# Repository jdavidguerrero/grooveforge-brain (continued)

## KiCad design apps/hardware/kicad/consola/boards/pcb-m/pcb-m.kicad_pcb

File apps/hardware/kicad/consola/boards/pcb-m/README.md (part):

# PCB-M — Placa Principal GrooveForge Consola

> Esquemático jerárquico KiCad 10, decisiones **D8–D43 aprobadas por Juan (2026-11-12; D40 actualizado 2026-11-13)**
> (`apps/docs/consola/24-placa-principal.md` §8). Sin layout PCB; no es aprobación de fabricación.
> Descripción eléctrica: `tools/schgen/pcb_m.py`. Firmware: `apps/consola/surface/include/consola_s/ConsolaMap.h`
> y `apps/docs/consola/17-mapa-pines-teensy.md`. Conector fabricado: `../CONNECTORS.md`.

No habrá PCB-N: jog, pots IN/CUE/MASTER, selector y audífonos son componentes de panel por cable.
PCB-M no lleva MCP23017: **0x20 está en PCB-A; 0x21/0x22/0x23 en la PCB-K única**, que reemplaza
K1/K2. JOG_A/B van a Teensy 37/40; JOG_CLICK y PEDAL_BTN viajan por J_PCB_K al MCP 0x23.

## Bloques (10 subhojas)

| # | Hoja | Contenido |
|---|---|---|
| 01 | `01-teensy` | Sockets Teensy 4.1 y Audio Shield Rev D (módulos); I2S interno |
| 02 | `02-analog-front` | Frente Studio: pad 33k/12k/5.1k, polos A/B del selector por cable, acople 1µF, 1k, BAT54S, bias 100k a VREF; MCP6004 seguidores L/R/VREF; LINE OUT 10µF + 47k sin buffer; divisor PAD_SEL 10k/10k |
| 03 | `03-adc` | ADS1115 0x48 faders AIN0–3; 0x49 expresión/Sharp |
| 04 | `04-mcp-io` | **Vacía**, reservada; MCP 0x23 vive en PCB-K |
| 05 | `05-cv-dac` | MCP4725 0x60/0x61, MCP6004 ganancia 1,5; 1k serie + BAT54S por CV |
| 06 | `06-surface` | JST-PH para jog, pots, selector, HP y FSR; RC 1k/100nF por pot |
| 07 | `07-midi` | **Todo DNP**, reserva sin agujeros/mazos: opto 6N138 y polarización; JST-PH para MIDI TRS **tipo A**, OUT 33Ω/10Ω |
| 08 | `08-connectors-panel` | IDC PCB-A, Qwiic, Serial7 M4, PCB-K, Sharp/expresión |
| 09 | `09-connectors-rear` | JST-PH hacia LINE IN/OUT, CV, pedal; E-drum DNP |
| 11 | `11-diagnostics` | TP, puentes de servicio, indicadores y selección de pull-ups locales |
| 12 | `12-i2c-branches` | PCA9517A ×2, EN_K pin0 / EN_A pin1, pull-ups B, 47 Ω y USBLC6-2SC6 |
| 10 | `10-power` | J_5V_LED_IN → F1; LDO +3.3VA; NT1 AGND/GND; buffer LED y pull-ups I2C |

## Cross-reference: Teensy ↔ señales de PCB-A y panel (D8)

**Manda el pinout de PCB-A ya fabricada**, no la antigua columna Teensy de CONNECTORS.md.
Cinta IDC **1:1**. PCB-M distribuye cada señal al pin que usa el firmware actual:

| Teensy | Función | Net PCB-M | Ruta |
|---|---|---|---|
| T0 / T1 | EN_K / EN_A | `EN_K_GPIO` / `EN_A_GPIO` | Cada rama por su SJ_EN_K_GPIO / SJ_EN_A_GPIO y pull-up 10k (D30); MIDI DNP |
| T2 / T3 | ENC1 A/B | `ENC1_A` / `ENC1_B` | J1_PCBA **5 / 7** |
| T4 / T5 | ENC2 A/B | `ENC2_A` / `ENC2_B` | J1_PCBA **9 / 10** |
| T6 / T9 | ENC3 A/B | `ENC3_A` / `ENC3_B` | J1_PCBA **13 / 15** |
| T10 / T11 | ENC4 A/B | `ENC4_A` / `ENC4_B` | J1_PCBA **17 / 19** |
| T12 / T30 | ENC5 A/B | `ENC5_A` / `ENC5_B` | J1_PCBA **8 / 21** |
| T31 / T32 | ENC6 A/B | `ENC6_A` / `ENC6_B` | J1_PCBA **23 / 25** |
| T33 / T34 | ENC7 A/B | `ENC7_A` / `ENC7_B` | J1_PCBA **28 / 29** |
| T35 / T36 | ENC8 A/B | `ENC8_A` / `ENC8_B` | J1_PCBA **27 / 24** |
| T13 | LEDs teclas | `LED_DATA` | 74AHCT1G125 → `LED_DIN_5V` → **J_PCB_K.6**; J1.26 NC |
| T14–T17 | FSR velocity 1–4 | `FSR1_ADC`–`FSR4_ADC` | J_FSR1–4, divisor 10k a GND |
| T18 / T19 | I2C SDA/SCL | `I2C_SDA` / `I2C_SCL` | lado A de PCA9517A y convertidores; B_A → J2_I2C.3/.4; B_K → J_PCB_K.2/.4 |
| T22 | MASTER | `POT_MASTER` | J_POT_MASTER.2 → **1k → ADC; 100nF a GND** |
| T24 | CUE | `POT_CUE` | J_POT_CUE.2 → **1k → ADC; 100nF a GND** |
| T26 | IN | `POT_IN` | J_POT_IN.2 → **1k → ADC; 100nF a GND** |
| T28 / T29 | M4 RX/TX Serial7 | `M4_RX7` / `M4_TX7` | J3_M4.3 / .4 ↔ pads SDA/TX M4 / SCL/RX M4, vía 1 kΩ cada línea |
| T37 / T40 | Jog A/B | `JOG_A` / `JOG_B` | J_JOG.2/.3; clic por .4 hacia PCB-K |
| T41 | Selector pad | `PAD_SEL_ADC` | J_PAD_SEL.2 y divisor permanente 10k/10k |
| T7 / T8 / T20 / T21 / T23 | I2S TX/RX/LRCLK/BCLK/MCLK | `I2S_*` | Internos al módulo Audio Shield; sin ruta al panel |
| T25 / T27 / T38 / T39 | E-drum reservado | NC | No se asigna función nueva; J_EDRUM DNP |

| Señal de PCB-A | J1_PCBA | Destino PCB-M |
|---|---|---|
| FADER1 / FADER2 / FADER3 / FADER4 | **16 / 14 / 12 / 11** | U_ADS1 **AIN0 / AIN1 / AIN2 / AIN3** (pines 4/5/6/7), dirección **0x48** |
| +5V | 1 / 2 | +5V_LED después de F1 |
| GND | 3 / 4 / 6 | GND |
| +3V3 | 30 | +3.3V digital |
| Spare | **18** | **NC**, sin uso |
| INT_K / INT_A | **20 / 22** | **NC**, MCP por sondeo I2C |
| LED_DIN | **26** | **NC**, LED solo por J_PCB_K |

**I2C no va por el IDC J1:** llega a PCB-A por J2. La PCB-A fabricada no se modifica salvo
**desoldar R1/R2** al instalar PCB-M (D14). No conectar además la antigua cadena PCB-A J4 → K1/K2
al usar la nueva PCB-K por J_PCB_K.

## Conectores hacia panel y otras placas

PH = JST-PH 2,0 mm; normalmente BnB-PH-K vertical. J_5V_LED_IN usa S2B-PH-K horizontal de la BOM.

| Ref | Tipo | Pines en orden 1→n |
|---|---|---|
| J1_PCBA | IDC 2×15 | Pinout fabricado de CONNECTORS.md; destinos en tablas anteriores |
| J2_I2C | JST-SH 4 Qwiic | GND / +3.3V / SDA / SCL |
| J3_M4 | PH 4 | GND / **NC** / M4_RX7_CABLE / M4_TX7_CABLE; pads M4 por rótulo (D40), vía 1 kΩ por señal; M4 por USB propio |
| J_PCB_K | PH 10 C158038 | +3.3V / SDA_B_K / GND / SCL_B_K / GND / LED_DIN_5V / GND / +5V_LED_K / JOG_CLICK / PEDAL_BTN |
| J5_SHARP1, J6_SHARP2 | PH 3 cada uno | +5V_LED / SHARPx_RAW / GND; 10k serie hacia ADS |
| J7_EXP1, J8_EXP2 | PH 2 cada uno | +3.3V / EXPx_ADC, pulldown 10k |
| J_JOG | PH 4 | GND / JOG_A / JOG_B / JOG_CLICK |
| J_POT_MASTER/CUE/IN | PH 3 cada uno | +3.3V / POT_x_WIPER / GND; cursor **antes** del RC |
| J_PAD_SEL | PH 3 | +3.3V / PAD_SEL_ADC / GND |
| J_FSR1–4 | PH 2 cada uno | +3.3V / FSRx_ADC; pulldown 10k |
| J_5V_LED_IN | PH 2 S2B-PH-K | **+5V_LED_RAW / GND** desde cable USB-A del Pi |
| J_5V_BKUP | PH 2, **DNP** | +5V_LED_RAW / GND; solo alternativa, no conectar ambas entradas |
| J_EDRUM | PH 5, **DNP** | Todos NC |

### Cableado jack ↔ JST-PH (D15)

Los jacks se compran en **Bogotá**, se fijan **con tuerca a la pared trasera del cuerpo** y van
por cable a los JST-PH del borde trasero de PCB-M. No hay jacks montados en esta PCB. Las hojas
06/07/09 son agrupaciones eléctricas: colocar J_HP en el borde trasero; JST MIDI DNP, sin mazos ni agujeros
cuando se haga layout. Confirmar por continuidad los terminales del jack comprado antes de soldar;
la tabla usa **T = tip/punta, R = ring/anillo, S = sleeve/manguito**, no la numeración de sus patillas.

| Jack externo | Ref en PCB-M | JST-PH | Cableado hacia contactos del jack |
|---|---|---|---|
| LINE IN L 6,35 mm TRS | J_LINE_IN_L | B3B-PH-K, 3 vías | **1→T** LINE_IN_L_T, **2→R** LINE_IN_L_R, **3→S** AGND |
| LINE IN R 6,35 mm TRS | J_LINE_IN_R | B3B-PH-K, 3 vías | **1→T** LINE_IN_R_T, **2→R** LINE_IN_R_R, **3→S** AGND |
| LINE OUT L 6,35 mm TS/TRS | J_LINE_OUT_L | B3B-PH-K, 3 vías | **1→T** LINE_OUT_L_T después de 10µF, **2 NC**, **3→S** AGND; ring sin cable si es TRS |
| LINE OUT R 6,35 mm TS/TRS | J_LINE_OUT_R | B3B-PH-K, 3 vías | **1→T** LINE_OUT_R_T después de 10µF, **2 NC**, **3→S** AGND; ring sin cable si es TRS |
| PEDAL 6,35 mm TRS | J_PEDAL | B3B-PH-K, 3 vías | **1→T** PEDAL_RAW (1k → PEDAL_BTN protegido), **2 NC** (R sin cable), **3→S** GND |
| CV1 3,5 mm TS | J_CV1 | B2B-PH-K, 2 vías | **1→T** CV1_PROTECTED, **2→S** AGND |
| CV2 3,5 mm TS | J_CV2 | B2B-PH-K, 2 vías | **1→T** CV2_PROTECTED, **2→S** AGND |
| MIDI IN 3,5 mm TRS **tipo A** | J_MIDI_IN | B3B-PH-K, 3 vías | **1→T** MIDI_IN_TIP (DIN5), **2→R** MIDI_IN_RING (DIN4), **3 NC** (sleeve/DIN2 sin cable) |
| MIDI OUT 3,5 mm TRS **tipo A** | J_MIDI_OUT | B3B-PH-K, 3 vías | **1→T** MIDI_OUT_TIP (DIN5), **2→R** MIDI_OUT_RING (DIN4), **3→S** GND (DIN2) |
| Audífonos cue 6,35 mm TRS | **J_HP** (06) | B3B-PH-K, 3 vías | **1→T** HP_L, **2→R** HP_R, **3→S** HP_VGND |

**HP_VGND es una salida activa del SGTL5000, nunca GND/AGND.** Se elimina el duplicado J_HP_CUE:
J_HP es el único conector hacia el jack de audífonos que ya iba por cable.
**Detección de inserción:** los símbolos anteriores eran AudioJack2/3 sin switches; ninguno tenía
pin ni red de detección. Por tanto se conservan todos sus contactos actuales y no se inventa un
pin de detección. Si el jack adquirido trae contactos conmutados, dejarlos sin cable y verificar
que T/R/S se identificaron correctamente. **LINE IN ring sigue sin terminación balanceada definida**;
se conserva la red por cable, pendiente de decisión eléctrica antes de fabricar.

### Selector en panel (D13)

R_SEL_T/R_SEL_B de 10k quedan en PCB-M: +3.3V → 10k → **PAD_SEL_ADC** → 10k → GND.
Se elimina **SW_PAD_SEL**. Cablear el **común del polo C** a J_PAD_SEL.2, sus contactos extremos
a .3 (GND) y .1 (+3,3 V), y **dejar el contacto central sin cable**. Lectura 0 / 1,65 / 3,3 V;
no se necesita un cuarto hilo ni una escalera en el panel. La correspondencia con 0/−10/−20 dB
se verifica con los polos A/B y el firmware en banco.
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
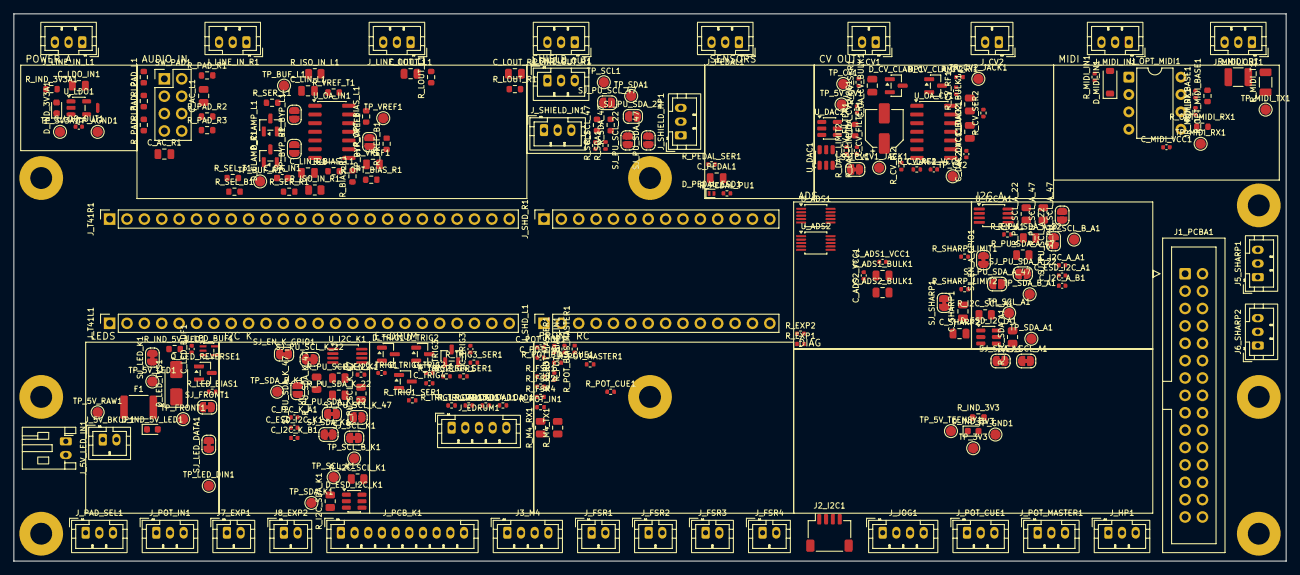
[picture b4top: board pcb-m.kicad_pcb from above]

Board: 2 copper layers, 186.0 x 80.0 mm, 254 parts (0 on the bottom side), 156 nets, no tracks yet.

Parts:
C_AC_L1: 1uF; C_0805_2012Metric
C_AC_R1: 1uF; C_0805_2012Metric
C_ADS1_BULK1, C_ADS2_BULK1: 10uF; C_0805_2012Metric
C_ADS1_VCC1, C_ADS2_VCC1: 100nF; C_0402_1005Metric
C_CV_FILTER1: 47uF 16V; CP_Elec_5x5.4
C_DAC1_BULK1, C_DAC2_BULK1: 10uF; C_0805_2012Metric
C_DAC1_VCC1, C_DAC2_VCC1: 100nF; C_0402_1005Metric
C_ESD_I2C_A1, C_ESD_I2C_K1: 100nF; C_0402_1005Metric
C_I2C_A_A1, C_I2C_A_B1, C_I2C_K_A1, C_I2C_K_B1: 100nF; C_0402_1005Metric
C_LDO_IN1: 10uF; C_0805_2012Metric
C_LDO_OUT1: 1uF; C_0402_1005Metric
C_LED_BUF1: 100nF; C_0402_1005Metric
C_LIN_L1: 4.7uF; C_0805_2012Metric
C_LIN_R1: 4.7uF; C_0805_2012Metric
C_LOUT_L1: 10uF; C_0805_2012Metric
C_LOUT_R1: 10uF; C_0805_2012Metric
C_MIDI_VCC1: 100nF; C_0402_1005Metric
C_OA_CV_BULK1: 10uF; C_0805_2012Metric
C_OA_CV_VCC1: 100nF; C_0402_1005Metric
C_OA_IN1: 100nF; C_0603_1608Metric
C_PEDAL1: 10nF; C_0805_2012Metric
C_POT_CUE1: 100nF; C_0402_1005Metric
C_POT_IN1: 100nF; C_0402_1005Metric
C_POT_MASTER1: 100nF; C_0402_1005Metric
C_SHARP1, C_SHARP2: 10uF; C_0805_2012Metric
C_TRIG1, C_TRIG2, C_TRIG3, C_TRIG4: DNP; C_0402_1005Metric
C_VREF1: 10uF; C_0805_2012Metric
D_CLAMP_L1: BAT54S; SOT-23
D_CLAMP_R1: BAT54S; SOT-23
D_CV_CLAMP1, D_CV_CLAMP2: BAT54S; SOT-23
D_ESD_I2C_A1, D_ESD_I2C_K1: USBLC6-2SC6; SOT-23-6
D_IND_3V3, D_IND_3V3A1, D_IND_5V_LED1: RED ~1mA; LED_0603_1608Metric
D_LED_TVS1: SMAJ5.0A; D_SMA_K1
D_MIDI_IN1: 1N4148W; D_SOD-123
D_PEDAL_ESD1: PESD3V3U1UL,315; D_SOD-882_K1
D_TRIG1, D_TRIG2, D_TRIG3, D_TRIG4: BAT54S; SOT-23
F1: 0.75A MF-MSMF075/24-2; Fuse_1812_4532Metric
H1, H2, H3, H4, H5, H6, H7, H8: M3 to floor tower; MountingHole_3.2mm_M3_Pad
J1_PCBA1: IDC_2x15_PCB-A; IDC-Header_2x15_P2.54mm_Vertical
J2_I2C1: JST-SH_4pin_I2C; JST_SH_SM04B-SRSS-TB_1x04-1MP_P1.00mm_Horizontal
J3_M4: JST-PH_4pin_M4; JST_PH_B4B-PH-K_1x04_P2.00mm_Vertical
J5_SHARP1: JST-PH_3pin_Sharp1; JST_PH_B3B-PH-K_1x03_P2.00mm_Vertical
J6_SHARP2: JST-PH_3pin_Sharp2; JST_PH_B3B-PH-K_1x03_P2.00mm_Vertical
J7_EXP1: JST-PH_2pin_EXP1; JST_PH_B2B-PH-K_1x02_P2.00mm_Vertical
J8_EXP2: JST-PH_2pin_EXP2; JST_PH_B2B-PH-K_1x02_P2.00mm_Vertical
JP_BYP_L1: BYP L (sin U_OA_IN); SolderJumper-2_P1.3mm_Open_RoundedPad1.0x1.5mm
JP_BYP_R1: BYP R (sin U_OA_IN); SolderJumper-2_P1.3mm_Open_RoundedPad1.0x1.5mm
JP_BYP_VREF1: BYP VREF (sin U_OA_IN); SolderJumper-2_P1.3mm_Open_RoundedPad1.0x1.5mm
J_5V_BKUP1: 5V_BACKUP_DNP; JST_PH_B2B-PH-K_1x02_P2.00mm_Vertical
J_5V_LED_IN1: USB-A_PI_5V_LED_IN; JST_PH_S2B-PH-K_1x02_P2.00mm_Horizontal
J_CV1: CV1_PANEL_CABLE; JST_PH_B2B-PH-K_1x02_P2.00mm_Vertical
J_CV2: CV2_PANEL_CABLE; JST_PH_B2B-PH-K_1x02_P2.00mm_Vertical
J_EDRUM1: EDRUM_RESERVED_DNP; JST_PH_B5B-PH-K_1x05_P2.00mm_Vertical
J_FSR1: JST-PH_2pin_FSR1; JST_PH_B2B-PH-K_1x02_P2.00mm_Vertical
J_FSR2: JST-PH_2pin_FSR2; JST_PH_B2B-PH-K_1x02_P2.00mm_Vertical
J_FSR3: JST-PH_2pin_FSR3; JST_PH_B2B-PH-K_1x02_P2.00mm_Vertical
J_FSR4: JST-PH_2pin_FSR4; JST_PH_B2B-PH-K_1x02_P2.00mm_Vertical
J_HP1: HP_CABLE; JST_PH_B3B-PH-K_1x03_P2.00mm_Vertical
J_JOG1: JOG_CABLE; JST_PH_B4B-PH-K_1x04_P2.00mm_Vertical
J_LINE_IN_L1: LINE_IN_L_PANEL_CABLE; JST_PH_B3B-PH-K_1x03_P2.00mm_Vertical
J_LINE_IN_R1: LINE_IN_R_PANEL_CABLE; JST_PH_B3B-PH-K_1x03_P2.00mm_Vertical
J_LINE_OUT_L1: LINE_OUT_L_PANEL_CABLE; JST_PH_B3B-PH-K_1x03_P2.00mm_Vertical
J_LINE_OUT_R1: LINE_OUT_R_PANEL_CABLE; JST_PH_B3B-PH-K_1x03_P2.00mm_Vertical
J_MIDI_IN1: MIDI_IN_PANEL_CABLE; JST_PH_B3B-PH-K_1x03_P2.00mm_Vertical
J_MIDI_OUT1: MIDI_OUT_PANEL_CABLE; JST_PH_B3B-PH-K_1x03_P2.00mm_Vertical
J_PAD_SEL1: PAD_SEL_CABLE; JST_PH_B3B-PH-K_1x03_P2.00mm_Vertical
J_PCB_K1: PCB_K_KEY_CABLE; JST_PH_B10B-PH-K_1x10_P2.00mm_Vertical
J_PEDAL1: PEDAL_PANEL_CABLE; JST_PH_B3B-PH-K_1x03_P2.00mm_Vertical
J_POT_CUE1: POT_CUE_CABLE; JST_PH_B3B-PH-K_1x03_P2.00mm_Vertical
J_POT_IN1: POT_IN_CABLE; JST_PH_B3B-PH-K_1x03_P2.00mm_Vertical
J_POT_MASTER1: POT_MASTER_CABLE; JST_PH_B3B-PH-K_1x03_P2.00mm_Vertical
J_SHD_L1: AudioShieldRevD-L; PinSocket_1x14_P2.54mm_Vertical
J_SHD_R1: AudioShieldRevD-R; PinSocket_1x14_P2.54mm_Vertical
J_SHIELD_HP1: HP L/R/VGND - NEVER GND; JST_PH_B3B-PH-K_1x03_P2.00mm_Vertical
J_SHIELD_IN1: SHIELD pads LINE IN L/R/G; JST_PH_B3B-PH-K_1x03_P2.00mm_Vertical
J_SHIELD_OUT1: SHIELD pads LINE OUT L/R/G; JST_PH_B3B-PH-K_1x03_P2.00mm_Vertical
J_T41L1: Teensy41-LeftRow; PinSocket_1x24_P2.54mm_Vertical
J_T41R1: Teensy41-RightRow; PinSocket_1x24_P2.54mm_Vertical
NT1: NetTie_2; NetTie-2_SMD_Pad0.5mm
Q_LED_REVERSE1: AO3401A; SOT-23
R_BIAS_L1: 100k; R_0603_1608Metric
R_BIAS_R1: 100k; R_0603_1608Metric
R_CV_FILTER1: 10; R_0603_1608Metric
R_CV_RF1, R_CV_RF2: 10k; R_0402_1005Metric
R_CV_RI1, R_CV_RI2: 20k; R_0402_1005Metric
R_CV_SER1, R_CV_SER2: 1k; R_0402_1005Metric
R_DAC_LIMIT1, R_DAC_LIMIT2: 2.2k; R_0402_1005Metric
R_EN_A1: 10k; R_0402_1005Metric
R_EN_K1: 10k; R_0402_1005Metric
R_EXP1, R_EXP2: 10k; R_0402_1005Metric
R_FSR1, R_FSR2, R_FSR3, R_FSR4: 10k; R_0402_1005Metric
R_I2C_SCL_A1, R_I2C_SCL_K1, R_I2C_SDA_A1, R_I2C_SDA_K1: 47; R_0805_2012Metric
R_IND_3V3, R_IND_3V3A1: 1.5k; R_0603_1608Metric
R_IND_5V_LED1: 3.3k; R_0603_1608Metric
R_ISO_IN_L1: 0; R_0805_2012Metric
R_ISO_IN_R1: 0; R_0805_2012Metric
R_LED_BIAS1: 100k; R_0402_1005Metric
R_LOUT_L1: 47k; R_0603_1608Metric
R_LOUT_R1: 47k; R_0603_1608Metric
R_M4_RX1, R_M4_TX1: 1k; R_0805_2012Metric
R_MIDI_BASE1: 10k; R_0402_1005Metric
R_MIDI_IN1: 220; R_0402_1005Metric
R_MIDI_R1: 33; R_1210_3225Metric
R_MIDI_RX1: 4.7k; R_0402_1005Metric
R_MIDI_T1: 10; R_1206_3216Metric
R_OPT_BIAS_L1: DNP tune parallel; R_0603_1608Metric
R_OPT_BIAS_R1: DNP tune parallel; R_0603_1608Metric
R_OPT_MIDI_BASE1: DNP tune parallel; R_0603_1608Metric
R_OPT_MIDI_RX1: DNP tune parallel; R_0603_1608Metric
R_PAD_L1: 33k; R_0603_1608Metric
R_PAD_L2: 12k; R_0603_1608Metric
R_PAD_L3: 5.1k; R_0603_1608Metric
R_PAD_R1: 33k; R_0603_1608Metric
R_PAD_R2: 12k; R_0603_1608Metric
R_PAD_R3: 5.1k; R_0603_1608Metric
R_PEDAL_PU1: 10k; R_0402_1005Metric
R_PEDAL_SER1: 1k; R_0402_1005Metric
R_POT_BIAS_CUE1: 100k; R_0402_1005Metric
R_POT_BIAS_IN1: 100k; R_0402_1005Metric
R_POT_BIAS_MASTER1: 100k; R_0402_1005Metric
R_POT_CUE1: 1k; R_0402_1005Metric
R_POT_IN1: 1k; R_0402_1005Metric
R_POT_MASTER1: 1k; R_0402_1005Metric
R_PU_SCL_A_22: 2.2k; R_0805_2012Metric
R_PU_SCL_A_47: 4.7k; R_0805_2012Metric
R_PU_SCL_K_22: 2.2k; R_0805_2012Metric
R_PU_SCL_K_47: 4.7k; R_0805_2012Metric
R_PU_SDA_A_22: 2.2k; R_0805_2012Metric
R_PU_SDA_A_47: 4.7k; R_0805_2012Metric
R_PU_SDA_K_22: 2.2k; R_0805_2012Metric
R_PU_SDA_K_47: 4.7k; R_0805_2012Metric
R_SCL1: 2.2k; R_0402_1005Metric
R_SCL_47: 4.7k; R_0603_1608Metric
R_SDA1: 2.2k; R_0402_1005Metric
R_SDA_47: 4.7k; R_0603_1608Metric
R_SEL_B1: 10k; R_0603_1608Metric
R_SEL_T1: 10k; R_0603_1608Metric
R_SER_L1: 1k; R_0603_1608Metric
R_SER_R1: 1k; R_0603_1608Metric
R_SHARP_LIMIT1, R_SHARP_LIMIT2: 10k; R_0402_1005Metric
R_TRIG1_LOAD1, R_TRIG2_LOAD1, R_TRIG3_LOAD1, R_TRIG4_LOAD1: 1M; R_0402_1005Metric
R_TRIG1_SER1, R_TRIG2_SER1, R_TRIG3_SER1, R_TRIG4_SER1: 1k; R_0402_1005Metric
R_VREF_B1: 10k; R_0603_1608Metric
R_VREF_T1: 10k; R_0603_1608Metric
SJ_CV1: SJ_CV; SolderJumper-2_P1.3mm_Bridged_RoundedPad1.0x1.5mm
SJ_EN_A_GPIO1: SJ_EN_A_GPIO; SolderJumper-2_P1.3mm_Bridged_RoundedPad1.0x1.5mm
SJ_EN_K_GPIO1: SJ_EN_K_GPIO; SolderJumper-2_P1.3mm_Bridged_RoundedPad1.0x1.5mm
SJ_FRONT1: SJ_FRONT; SolderJumper-2_P1.3mm_Bridged_RoundedPad1.0x1.5mm
SJ_LED_DATA1: SJ_LED_DATA; SolderJumper-2_P1.3mm_Bridged_RoundedPad1.0x1.5mm
SJ_LED_K1: SJ_LED_K; SolderJumper-2_P1.3mm_Bridged_RoundedPad1.0x1.5mm
SJ_PU_SCL_22: SJ_PU_SCL_22; SolderJumper-2_P1.3mm_Open_RoundedPad1.0x1.5mm
SJ_PU_SCL_47: SJ_PU_SCL_47; SolderJumper-2_P1.3mm_Open_RoundedPad1.0x1.5mm
SJ_PU_SCL_A_22: SJ_PU_SCL_A_22; SolderJumper-2_P1.3mm_Bridged_RoundedPad1.0x1.5mm
SJ_PU_SCL_A_47: SJ_PU_SCL_A_47; SolderJumper-2_P1.3mm_Open_RoundedPad1.0x1.5mm
SJ_PU_SCL_K_22: SJ_PU_SCL_K_22; SolderJumper-2_P1.3mm_Bridged_RoundedPad1.0x1.5mm
SJ_PU_SCL_K_47: SJ_PU_SCL_K_47; SolderJumper-2_P1.3mm_Open_RoundedPad1.0x1.5mm
SJ_PU_SDA_22: SJ_PU_SDA_22; SolderJumper-2_P1.3mm_Open_RoundedPad1.0x1.5mm
SJ_PU_SDA_47: SJ_PU_SDA_47; SolderJumper-2_P1.3mm_Open_RoundedPad1.0x1.5mm
SJ_PU_SDA_A_22: SJ_PU_SDA_A_22; SolderJumper-2_P1.3mm_Bridged_RoundedPad1.0x1.5mm
SJ_PU_SDA_A_47: SJ_PU_SDA_A_47; SolderJumper-2_P1.3mm_Open_RoundedPad1.0x1.5mm
SJ_PU_SDA_K_22: SJ_PU_SDA_K_22; SolderJumper-2_P1.3mm_Bridged_RoundedPad1.0x1.5mm
SJ_PU_SDA_K_47: SJ_PU_SDA_K_47; SolderJumper-2_P1.3mm_Open_RoundedPad1.0x1.5mm
SJ_SCL_A1: SJ_SCL_A; SolderJumper-2_P1.3mm_Bridged_RoundedPad1.0x1.5mm
SJ_SCL_K1: SJ_SCL_K; SolderJumper-2_P1.3mm_Bridged_RoundedPad1.0x1.5mm
SJ_SDA_A1: SJ_SDA_A; SolderJumper-2_P1.3mm_Bridged_RoundedPad1.0x1.5mm
SJ_SDA_K1: SJ_SDA_K; SolderJumper-2_P1.3mm_Bridged_RoundedPad1.0x1.5mm
SJ_SHARP1: SJ_SHARP; SolderJumper-2_P1.3mm_Bridged_RoundedPad1.0x1.5mm
SW_PAD1: PAD 3P3T A/B; PinHeader_2x04_P2.54mm_Vertical
TP_3V3: +3.3V; TestPoint_Pad_D1.5mm
TP_3V3A1: +3.3VA; TestPoint_Pad_D1.5mm
TP_5V_CV1: +5V_CV; TestPoint_Pad_D1.5mm
TP_5V_LED1: +5V_LED; TestPoint_Pad_D1.5mm
TP_5V_RAW1: +5V_LED_RAW; TestPoint_Pad_D1.5mm
TP_5V_TEENSY1: +5V_TEENSY; TestPoint_Pad_D1.5mm
TP_AGND1: AGND; TestPoint_Pad_D1.5mm
TP_BUF_L1: BUF_L; TestPoint_Pad_D1.5mm
TP_BUF_R1: BUF_R; TestPoint_Pad_D1.5mm
TP_CV1: CV1_OUT; TestPoint_Pad_D1.5mm
TP_CV1_JACK1: CV1_PROTECTED; TestPoint_Pad_D1.5mm
TP_CV2: CV2_OUT; TestPoint_Pad_D1.5mm
TP_CV2_JACK1: CV2_PROTECTED; TestPoint_Pad_D1.5mm
TP_FRONT1: +3.3VA_FRONT; TestPoint_Pad_D1.5mm
TP_GND1: GND; TestPoint_Pad_D1.5mm
TP_LED_DIN1: LED_DIN_5V; TestPoint_Pad_D1.5mm
TP_MIDI_RX1: MIDI_RX; TestPoint_Pad_D1.5mm
TP_MIDI_TX1: MIDI_TX; TestPoint_Pad_D1.5mm
TP_SCL1: I2C_SCL; TestPoint_Pad_D1.5mm
TP_SCL_A1: I2C_SCL_A; TestPoint_Pad_D1.5mm
TP_SCL_B_A1: I2C_SCL_B_A; TestPoint_Pad_D1.5mm
TP_SCL_B_K1: I2C_SCL_B_K; TestPoint_Pad_D1.5mm
TP_SCL_K1: I2C_SCL_K; TestPoint_Pad_D1.5mm
TP_SDA1: I2C_SDA; TestPoint_Pad_D1.5mm
TP_SDA_A1: I2C_SDA_A; TestPoint_Pad_D1.5mm
TP_SDA_B_A1: I2C_SDA_B_A; TestPoint_Pad_D1.5mm
TP_SDA_B_K1: I2C_SDA_B_K; TestPoint_Pad_D1.5mm
TP_SDA_K1: I2C_SDA_K; TestPoint_Pad_D1.5mm
TP_VREF1: VREF; TestPoint_Pad_D1.5mm
U_ADS1, U_ADS2: ADS1115IDGSR; TSSOP-10_3x3mm_P0.5mm
U_DAC1, U_DAC2: MCP4725A0T-E/CH; SOT-23-6
U_I2C_A1, U_I2C_K1: PCA9517ADP,118; MSOP-8_3x3mm_P0.65mm
U_LDO1: TLV75533PDBV; SOT-23-5
U_LED_BUF1: 74AHCT1G125; SOT-353_SC-70-5
U_OA_CV1: MCP6004; SOIC-14_3.9x8.7mm_P1.27mm
U_OA_IN1: MCP6004; SOIC-14_3.9x8.7mm_P1.27mm
U_OPT_MIDI1: 6N138; DIP-8_W7.62mm

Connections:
+3.3V: C_DAC1_BULK1.1, C_DAC1_VCC1.1, C_DAC2_BULK1.1, C_DAC2_VCC1.1, C_ESD_I2C_A1.1, C_ESD_I2C_K1.1, C_I2C_A_A1.1, C_I2C_A_B1.1, C_I2C_K_A1.1, C_I2C_K_B1.1, D_ESD_I2C_A1.5, D_ESD_I2C_K1.5, D_TRIG1.2, D_TRIG2.2, D_TRIG3.2, D_TRIG4.2, J1_PCBA1.30, J2_I2C1.2, J7_EXP1.1, J8_EXP2.1, J_FSR1.1, J_FSR2.1, J_FSR3.1, J_FSR4.1, J_PAD_SEL1.1, J_PCB_K1.1, J_POT_CUE1.1, J_POT_IN1.1, J_POT_MASTER1.1, J_SHD_R1.3, J_T41L1.15, J_T41R1.3, R_EN_A1.1, R_EN_K1.1, R_IND_3V3.1, R_MIDI_R1.1, R_MIDI_RX1.1, R_OPT_MIDI_RX1.1, R_PEDAL_PU1.1, R_SEL_T1.1, SJ_PU_SCL_22.1, SJ_PU_SCL_47.1, SJ_PU_SCL_A_22.1, SJ_PU_SCL_A_47.1, SJ_PU_SCL_K_22.1, SJ_PU_SCL_K_47.1, SJ_PU_SDA_22.1, SJ_PU_SDA_47.1, SJ_PU_SDA_A_22.1, SJ_PU_SDA_A_47.1, SJ_PU_SDA_K_22.1, SJ_PU_SDA_K_47.1, TP_3V3.1, U_DAC1.3, U_DAC2.3, U_DAC2.6, U_I2C_A1.1, U_I2C_A1.8, U_I2C_K1.1, U_I2C_K1.8
+3.3VA: C_ADS1_BULK1.1, C_ADS1_VCC1.1, C_ADS2_BULK1.1, C_ADS2_VCC1.1, C_LDO_OUT1.1, R_IND_3V3A1.1, SJ_FRONT1.1, TP_3V3A1.1, U_ADS1.8, U_ADS2.1, U_ADS2.8, U_LDO1.5
+3.3VA_FRONT: C_OA_IN1.1, D_CLAMP_L1.2, D_CLAMP_R1.2, R_VREF_T1.1, SJ_FRONT1.2, TP_FRONT1.1, U_OA_IN1.4
+5V_CV: C_CV_FILTER1.1, C_OA_CV_BULK1.1, C_OA_CV_VCC1.1, D_CV_CLAMP1.2, D_CV_CLAMP2.2, R_CV_FILTER1.2, TP_5V_CV1.1, U_OA_CV1.4
+5V_CV_IN: R_CV_FILTER1.1, SJ_CV1.2
+5V_LED: C_LED_BUF1.1, D_LED_TVS1.1, J1_PCBA1.1, J1_PCBA1.2, Q_LED_REVERSE1.2, R_IND_5V_LED1.1, SJ_LED_K1.1, SJ_SHARP1.1, TP_5V_LED1.1, U_LED_BUF1.5
+5V_LED_FUSED: F1.2, Q_LED_REVERSE1.3
+5V_LED_K: J_PCB_K1.8, SJ_LED_K1.2
+5V_LED_RAW: F1.1, J_5V_BKUP1.1, J_5V_LED_IN1.1, TP_5V_RAW1.1
+5V_LED_SHARP: C_SHARP1.1, C_SHARP2.1, J5_SHARP1.1, J6_SHARP2.1, SJ_SHARP1.2
+5V_TEENSY: C_LDO_IN1.1, C_MIDI_VCC1.1, J_T41R1.1, SJ_CV1.1, TP_5V_TEENSY1.1, U_LDO1.1, U_LDO1.3, U_OPT_MIDI1.8
/01-teensy/I2S_BCLK: J_SHD_R1.6, J_T41R1.6
/01-teensy/I2S_LRCLK: J_SHD_R1.7, J_T41R1.7
/01-teensy/I2S_MCLK: J_SHD_R1.4, J_T41R1.4
/01-teensy/I2S_RX: J_SHD_L1.10, J_T41L1.10
/01-teensy/I2S_TX: J_SHD_L1.9, J_T41L1.9
/02-analog-front/AC_L: C_AC_L1.2, R_SER_L1.1
/02-analog-front/AC_R: C_AC_R1.2, R_SER_R1.1
/02-analog-front/BUF_L: C_LIN_L1.1, JP_BYP_L1.2, TP_BUF_L1.1, U_OA_IN1.1, U_OA_IN1.2
/02-analog-front/BUF_R: C_LIN_R1.1, JP_BYP_R1.2, TP_BUF_R1.1, U_OA_IN1.6, U_OA_IN1.7
/02-analog-front/FRONT_LINE_IN_L: C_LIN_L1.2, R_ISO_IN_L1.1
/02-analog-front/FRONT_LINE_IN_R: C_LIN_R1.2, R_ISO_IN_R1.1
/02-analog-front/OA_IN_D: U_OA_IN1.13, U_OA_IN1.14
/02-analog-front/PAD_L: C_AC_L1.1, SW_PAD1.3
/02-analog-front/PAD_R: C_AC_R1.1, SW_PAD1.7
/02-analog-front/TAP10_L: R_PAD_L1.2, R_PAD_L2.1, SW_PAD1.2
/02-analog-front/TAP10_R: R_PAD_R1.2, R_PAD_R2.1, SW_PAD1.6
/02-analog-front/TAP20_L: R_PAD_L2.2, R_PAD_L3.1, SW_PAD1.4
/02-analog-front/TAP20_R: R_PAD_R2.2, R_PAD_R3.1, SW_PAD1.8
/02-analog-front/VREF_DIV: C_VREF1.1, JP_BYP_VREF1.1, R_VREF_B1.1, R_VREF_T1.2, U_OA_IN1.10
/05-cv-dac/CV1_FB: R_CV_RF1.2, R_CV_RI1.1, U_OA_CV1.2
/05-cv-dac/CV2_FB: R_CV_RF2.2, R_CV_RI2.1, U_OA_CV1.6
/05-cv-dac/CV_UNUSED_3: U_OA_CV1.8, U_OA_CV1.9
/05-cv-dac/CV_UNUSED_4: U_OA_CV1.13, U_OA_CV1.14
/05-cv-dac/DAC1_LIMITED: R_DAC_LIMIT1.2, U_OA_CV1.3
/05-cv-dac/DAC1_RAW: R_DAC_LIMIT1.1, U_DAC1.1
/05-cv-dac/DAC2_LIMITED: R_DAC_LIMIT2.2, U_OA_CV1.5
/05-cv-dac/DAC2_RAW: R_DAC_LIMIT2.1, U_DAC2.1
/06-surface/POT_CUE_WIPER: J_POT_CUE1.2, R_POT_CUE1.1
/06-surface/POT_IN_WIPER: J_POT_IN1.2, R_POT_IN1.1
/06-surface/POT_MASTER_WIPER: J_POT_MASTER1.2, R_POT_MASTER1.1
/07-midi/MIDI_IN_RING: J_MIDI_IN1.2, R_MIDI_IN1.1
/07-midi/MIDI_IN_TIP: D_MIDI_IN1.2, J_MIDI_IN1.1, U_OPT_MIDI1.3
/07-midi/MIDI_OPTO_A: D_MIDI_IN1.1, R_MIDI_IN1.2, U_OPT_MIDI1.2
/07-midi/MIDI_OUT_RING: J_MIDI_OUT1.2, R_MIDI_R1.2
/07-midi/MIDI_OUT_TIP: J_MIDI_OUT1.1, R_MIDI_T1.2
/08-connectors-panel/M4_RX7_CABLE: J3_M4.3, R_M4_RX1.2
/08-connectors-panel/M4_TX7_CABLE: J3_M4.4, R_M4_TX1.2
/08-connectors-panel/SHARP1_RAW: J5_SHARP1.2, R_SHARP_LIMIT1.1
/08-connectors-panel/SHARP2_RAW: J6_SHARP2.2, R_SHARP_LIMIT2.1
/09-connectors-rear/PEDAL_RAW: J_PEDAL1.1, R_PEDAL_SER1.1
/09-connectors-rear/TRIG1_J: J_EDRUM1.1, R_TRIG1_LOAD1.1, R_TRIG1_SER1.1
/09-connectors-rear/TRIG2_J: J_EDRUM1.2, R_TRIG2_LOAD1.1, R_TRIG2_SER1.1
/09-connectors-rear/TRIG3_J: J_EDRUM1.3, R_TRIG3_LOAD1.1, R_TRIG3_SER1.1
/09-connectors-rear/TRIG4_J: J_EDRUM1.4, R_TRIG4_LOAD1.1, R_TRIG4_SER1.1
/11-diagnostics/IND_3V3A_A: D_IND_3V3A1.2, R_IND_3V3A1.2
/11-diagnostics/IND_3V3_A: D_IND_3V3.2, R_IND_3V3.2
/11-diagnostics/IND_5V_LED_A: D_IND_5V_LED1.2, R_IND_5V_LED1.2
/11-diagnostics/PU_SCL_47: R_SCL_47.1, SJ_PU_SCL_47.2
/11-diagnostics/PU_SDA_47: R_SDA_47.1, SJ_PU_SDA_47.2
/12-i2c-branches/EN_A: R_EN_A1.2, SJ_EN_A_GPIO1.2, U_I2C_A1.5
/12-i2c-branches/EN_K: R_EN_K1.2, SJ_EN_K_GPIO1.2, U_I2C_K1.5
/12-i2c-branches/PU_SCL_A_22: R_PU_SCL_A_22.1, SJ_PU_SCL_A_22.2
/12-i2c-branches/PU_SCL_A_47: R_PU_SCL_A_47.1, SJ_PU_SCL_A_47.2
/12-i2c-branches/PU_SCL_K_22: R_PU_SCL_K_22.1, SJ_PU_SCL_K_22.2
/12-i2c-branches/PU_SCL_K_47: R_PU_SCL_K_47.1, SJ_PU_SCL_K_47.2
/12-i2c-branches/PU_SDA_A_22: R_PU_SDA_A_22.1, SJ_PU_SDA_A_22.2
/12-i2c-branches/PU_SDA_A_47: R_PU_SDA_A_47.1, SJ_PU_SDA_A_47.2
/12-i2c-branches/PU_SDA_K_22: R_PU_SDA_K_22.1, SJ_PU_SDA_K_22.2
/12-i2c-branches/PU_SDA_K_47: R_PU_SDA_K_47.1, SJ_PU_SDA_K_47.2
AGND: C_LDO_IN1.2, C_LDO_OUT1.2, C_OA_IN1.2, C_VREF1.2, D_CLAMP_L1.1, D_CLAMP_R1.1, D_IND_3V3A1.1, J_CV1.2, J_CV2.2, J_LINE_IN_L1.3, J_LINE_IN_R1.3, J_LINE_OUT_L1.3, J_LINE_OUT_R1.3, NT1.1, R_LOUT_L1.2, R_LOUT_R1.2, R_PAD_L3.2, R_PAD_R3.2, R_VREF_B1.2, TP_AGND1.1, U_LDO1.2, U_OA_IN1.11
CV1_OUT: R_CV_RF1.1, R_CV_SER1.1, TP_CV1.1, U_OA_CV1.1
CV1_PROTECTED: D_CV_CLAMP1.3, J_CV1.1, R_CV_SER1.2, TP_CV1_JACK1.1
CV2_OUT: R_CV_RF2.1, R_CV_SER2.1, TP_CV2.1, U_OA_CV1.7
CV2_PROTECTED: D_CV_CLAMP2.3, J_CV2.1, R_CV_SER2.2, TP_CV2_JACK1.1
ENC1_A: J1_PCBA1.5, J_T41L1.4
ENC1_B: J1_PCBA1.7, J_T41L1.5
ENC2_A: J1_PCBA1.9, J_T41L1.6
ENC2_B: J1_PCBA1.10, J_T41L1.7
ENC3_A: J1_PCBA1.13, J_T41L1.8
ENC3_B: J1_PCBA1.15, J_T41L1.11
ENC4_A: J1_PCBA1.17, J_T41L1.12
ENC4_B: J1_PCBA1.19, J_T41L1.13
ENC5_A: J1_PCBA1.8, J_T41L1.14
ENC5_B: J1_PCBA1.21, J_T41L1.22
ENC6_A: J1_PCBA1.23, J_T41L1.23
ENC6_B: J1_PCBA1.25, J_T41L1.24
ENC7_A: J1_PCBA1.28, J_T41R1.24
ENC7_B: J1_PCBA1.29, J_T41R1.23
ENC8_A: J1_PCBA1.27, J_T41R1.22
ENC8_B: J1_PCBA1.24, J_T41R1.21
EN_A_GPIO: J_T41L1.3, SJ_EN_A_GPIO1.1
EN_K_GPIO: J_T41L1.2, SJ_EN_K_GPIO1.1
EXP1_ADC: J7_EXP1.2, R_EXP1.1, U_ADS2.4
EXP2_ADC: J8_EXP2.2, R_EXP2.1, U_ADS2.5
FADER1_SIG: J1_PCBA1.16, U_ADS1.4
FADER2_SIG: J1_PCBA1.14, U_ADS1.5
FADER3_SIG: J1_PCBA1.12, U_ADS1.6
FADER4_SIG: J1_PCBA1.11, U_ADS1.7
FSR1_ADC: J_FSR1.2, J_T41R1.13, R_FSR1.1
FSR2_ADC: J_FSR2.2, J_T41R1.12, R_FSR2.1
FSR3_ADC: J_FSR3.2, J_T41R1.11, R_FSR3.1
FSR4_ADC: J_FSR4.2, J_T41R1.10, R_FSR4.1
GND: C_ADS1_BULK1.2, C_ADS1_VCC1.2, C_ADS2_BULK1.2, C_ADS2_VCC1.2, C_CV_FILTER1.2, C_DAC1_BULK1.2, C_DAC1_VCC1.2, C_DAC2_BULK1.2, C_DAC2_VCC1.2, C_ESD_I2C_A1.2, C_ESD_I2C_K1.2, C_I2C_A_A1.2, C_I2C_A_B1.2, C_I2C_K_A1.2, C_I2C_K_B1.2, C_LED_BUF1.2, C_MIDI_VCC1.2, C_OA_CV_BULK1.2, C_OA_CV_VCC1.2, C_PEDAL1.2, C_POT_CUE1.2, C_POT_IN1.2, C_POT_MASTER1.2, C_SHARP1.2, C_SHARP2.2, C_TRIG1.2, C_TRIG2.2, C_TRIG3.2, C_TRIG4.2, D_CV_CLAMP1.1, D_CV_CLAMP2.1, D_ESD_I2C_A1.2, D_ESD_I2C_K1.2, D_IND_3V3.1, D_IND_5V_LED1.1, D_LED_TVS1.2, D_PEDAL_ESD1.2, D_TRIG1.1, D_TRIG2.1, D_TRIG3.1, D_TRIG4.1, H1.1, H2.1, H3.1, H4.1, H5.1, H6.1, H7.1, H8.1, J1_PCBA1.3, J1_PCBA1.4, J1_PCBA1.6, J2_I2C1.1, J3_M4.1, J5_SHARP1.3, J6_SHARP2.3, J_5V_BKUP1.2, J_5V_LED_IN1.2, J_EDRUM1.5, J_JOG1.1, J_MIDI_OUT1.3, J_PAD_SEL1.3, J_PCB_K1.3, J_PCB_K1.5, J_PCB_K1.7, J_PEDAL1.3, J_POT_CUE1.3, J_POT_IN1.3, J_POT_MASTER1.3, J_SHD_L1.1, J_SHD_R1.2, J_SHIELD_IN1.3, J_SHIELD_OUT1.3, J_T41L1.1, J_T41R1.2, J_T41R1.15, NT1.2, Q_LED_REVERSE1.1, R_CV_RI1.2, R_CV_RI2.2, R_EXP1.2, R_EXP2.2, R_FSR1.2, R_FSR2.2, R_FSR3.2, R_FSR4.2, R_LED_BIAS1.2, R_MIDI_BASE1.2, R_OPT_MIDI_BASE1.2, R_POT_BIAS_CUE1.2, R_POT_BIAS_IN1.2, R_POT_BIAS_MASTER1.2, R_SEL_B1.2, R_TRIG1_LOAD1.2, R_TRIG2_LOAD1.2, R_TRIG3_LOAD1.2, R_TRIG4_LOAD1.2, TP_GND1.1, U_ADS1.1, U_ADS1.3, U_ADS2.3, U_DAC1.2, U_DAC1.6, U_DAC2.2, U_I2C_A1.4, U_I2C_K1.4, U_LED_BUF1.1, U_LED_BUF1.3, U_OA_CV1.10, U_OA_CV1.11, U_OA_CV1.12, U_OPT_MIDI1.5
HP_L: J_HP1.1, J_SHIELD_HP1.1
HP_R: J_HP1.2, J_SHIELD_HP1.2
HP_VGND: J_HP1.3, J_SHIELD_HP1.3
I2C_SCL: J_SHD_R1.8, J_T41R1.8, R_SCL1.2, R_SCL_47.2, TP_SCL1.1, U_ADS1.10, U_ADS2.10, U_DAC1.5, U_DAC2.5, U_I2C_A1.2, U_I2C_K1.2
I2C_SCL_A: D_ESD_I2C_A1.3, D_ESD_I2C_A1.4, J2_I2C1.4, R_I2C_SCL_A1.2, TP_SCL_A1.1
I2C_SCL_A_SER: R_I2C_SCL_A1.1, SJ_SCL_A1.2
I2C_SCL_B_A: R_PU_SCL_A_22.2, R_PU_SCL_A_47.2, SJ_SCL_A1.1, TP_SCL_B_A1.1, U_I2C_A1.7
I2C_SCL_B_K: R_PU_SCL_K_22.2, R_PU_SCL_K_47.2, SJ_SCL_K1.1, TP_SCL_B_K1.1, U_I2C_K1.7
I2C_SCL_K: D_ESD_I2C_K1.3, D_ESD_I2C_K1.4, J_PCB_K1.4, R_I2C_SCL_K1.2, TP_SCL_K1.1
I2C_SCL_K_SER: R_I2C_SCL_K1.1, SJ_SCL_K1.2
I2C_SDA: J_SHD_R1.9, J_T41R1.9, R_SDA1.2, R_SDA_47.2, TP_SDA1.1, U_ADS1.9, U_ADS2.9, U_DAC1.4, U_DAC2.4, U_I2C_A1.3, U_I2C_K1.3
I2C_SDA_A: D_ESD_I2C_A1.1, D_ESD_I2C_A1.6, J2_I2C1.3, R_I2C_SDA_A1.2, TP_SDA_A1.1
I2C_SDA_A_SER: R_I2C_SDA_A1.1, SJ_SDA_A1.2
I2C_SDA_B_A: R_PU_SDA_A_22.2, R_PU_SDA_A_47.2, SJ_SDA_A1.1, TP_SDA_B_A1.1, U_I2C_A1.6
I2C_SDA_B_K: R_PU_SDA_K_22.2, R_PU_SDA_K_47.2, SJ_SDA_K1.1, TP_SDA_B_K1.1, U_I2C_K1.6
I2C_SDA_K: D_ESD_I2C_K1.1, D_ESD_I2C_K1.6, J_PCB_K1.2, R_I2C_SDA_K1.2, TP_SDA_K1.1
I2C_SDA_K_SER: R_I2C_SDA_K1.1, SJ_SDA_K1.2
JOG_A: J_JOG1.2, J_T41R1.20
JOG_B: J_JOG1.3, J_T41R1.17
JOG_CLICK: J_JOG1.4, J_PCB_K1.9
LED_BUF_OUT: SJ_LED_DATA1.1, U_LED_BUF1.4
LED_DATA: J_T41R1.14, R_LED_BIAS1.1, U_LED_BUF1.2
LED_DIN_5V: J_PCB_K1.6, SJ_LED_DATA1.2, TP_LED_DIN1.1
LINE_IN_L_T: J_LINE_IN_L1.1, R_PAD_L1.1, SW_PAD1.1
LINE_IN_R_T: J_LINE_IN_R1.1, R_PAD_R1.1, SW_PAD1.5
LINE_OUT_L_T: C_LOUT_L1.2, J_LINE_OUT_L1.1, R_LOUT_L1.1
LINE_OUT_R_T: C_LOUT_R1.2, J_LINE_OUT_R1.1, R_LOUT_R1.1
M4_RX7: J_T41L1.20, R_M4_RX1.1
M4_TX7: J_T41L1.21, R_M4_TX1.1
MIDI_OPTO_BASE: R_MIDI_BASE1.1, R_OPT_MIDI_BASE1.1, U_OPT_MIDI1.7
MIDI_RX: R_MIDI_RX1.2, R_OPT_MIDI_RX1.2, TP_MIDI_RX1.1, U_OPT_MIDI1.6
MIDI_TX: R_MIDI_T1.1, TP_MIDI_TX1.1
PAD_SEL_ADC: J_PAD_SEL1.2, J_T41R1.16, R_SEL_B1.1, R_SEL_T1.2
PEDAL_BTN: C_PEDAL1.1, D_PEDAL_ESD1.1, J_PCB_K1.10, R_PEDAL_PU1.2, R_PEDAL_SER1.2
POT_CUE: C_POT_CUE1.1, J_T41L1.16, R_POT_BIAS_CUE1.1, R_POT_CUE1.2
POT_IN: C_POT_IN1.1, J_T41L1.18, R_POT_BIAS_IN1.1, R_POT_IN1.2
POT_MASTER: C_POT_MASTER1.1, J_T41R1.5, R_POT_BIAS_MASTER1.1, R_POT_MASTER1.2
PROT_L: D_CLAMP_L1.3, JP_BYP_L1.1, R_BIAS_L1.1, R_OPT_BIAS_L1.1, R_SER_L1.2, U_OA_IN1.3
PROT_R: D_CLAMP_R1.3, JP_BYP_R1.1, R_BIAS_R1.1, R_OPT_BIAS_R1.1, R_SER_R1.2, U_OA_IN1.5
PU_SCL_22: R_SCL1.1, SJ_PU_SCL_22.2
PU_SDA_22: R_SDA1.1, SJ_PU_SDA_22.2
SHARP1_ADC: R_SHARP_LIMIT1.2, U_ADS2.6
SHARP2_ADC: R_SHARP_LIMIT2.2, U_ADS2.7
SHIELD_LINE_IN_L: J_SHIELD_IN1.1, R_ISO_IN_L1.2
SHIELD_LINE_IN_R: J_SHIELD_IN1.2, R_ISO_IN_R1.2
SHIELD_LINE_OUT_L: C_LOUT_L1.1, J_SHIELD_OUT1.1
SHIELD_LINE_OUT_R: C_LOUT_R1.1, J_SHIELD_OUT1.2
TRIG1: C_TRIG1.1, D_TRIG1.3, J_T41L1.17, R_TRIG1_SER1.2
TRIG2: C_TRIG2.1, D_TRIG2.3, J_T41L1.19, R_TRIG2_SER1.2
TRIG3: C_TRIG3.1, D_TRIG3.3, J_T41R1.19, R_TRIG3_SER1.2
TRIG4: C_TRIG4.1, D_TRIG4.3, J_T41R1.18, R_TRIG4_SER1.2
VREF: JP_BYP_VREF1.2, R_BIAS_L1.2, R_BIAS_R1.2, R_OPT_BIAS_L1.2, R_OPT_BIAS_R1.2, TP_VREF1.1, U_OA_IN1.8, U_OA_IN1.9, U_OA_IN1.12

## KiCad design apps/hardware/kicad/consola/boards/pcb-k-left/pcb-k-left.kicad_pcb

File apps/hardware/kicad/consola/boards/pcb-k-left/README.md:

# PCB-K izquierda — GrooveForge Console

Layout terminado de dos capas y 1,6 mm; DRC entregado con **0 errores, 0 sin conectar y 0 diferencias de paridad**.
Los avisos de huella/serigrafía y las comprobaciones físicas pendientes se detallan en
[REPORT-k](../../tools/layout/REPORT-k.md). Este estado no equivale a aprobación CAM ni a validación del lote real.

La placa guardada es `pcb-k-left.kicad_pcb`; los Gerbers, taladros y el ZIP para PCB desnuda están en
[fab/](fab/). Usar esta entrega local, junto con su DRC en `docs/`, como fuente de fabricación.
`docs/` contiene además XML, PDF y ERC. Ver [doc 28](../../../../../docs/consola/28-pcb-k.md) para montaje.

`placement.csv` usa mm de panel, vista superior, +y hacia atrás. La transformación del layout es
**x_panel = x_KiCad + 44; y_panel = 371 − y_KiCad**. Rotaciones CCW KiCad; F = superior, B = inferior.
El LED queda a +4,93 mm del centro de tecla en y_panel. Las demás piezas van abajo.
Los soportes y los cuatro anclajes del marco M4 están definidos en el CSV de contornos y doc 28 §2.

## Montaje

**Choc V2 SOLDADAS directamente, sin zócalos**, según doc 28 **D-K1b** (Juan, 2026-11-13).
Las filas históricas key/socket de igual referencia representan una única huella mixta;
no comprar ni montar zócalos CPG135001S30. Los pads SMD asociados quedan sin uso.

Los JST PH THT **J1 y J2** van en la cara B: **recortar las colas a ≤0,8 mm sobre la cara de soldadura**
(cara superior, hacia la chapa). El máximo incluye todo metal y soldadura. Verificar cada pin con
calibre de altura o galga apoyada en el FR4 después de soldar y recortar; eliminar rebabas y comprobar
que ningún pico exceda 0,8 mm. Registrar la altura máxima antes de montar contra el aluminio.
La luz nominal a la chapa es solo **1,4 mm**, por lo que quedan **0,6 mm nominales**; comprobar también
la separación final con las tolerancias del apilado. No aceptar contacto con la chapa.

Para verificar el esquema desde la raíz: `python3 apps/hardware/kicad/consola/tools/check_netlist.py --board pcb-k-left`.

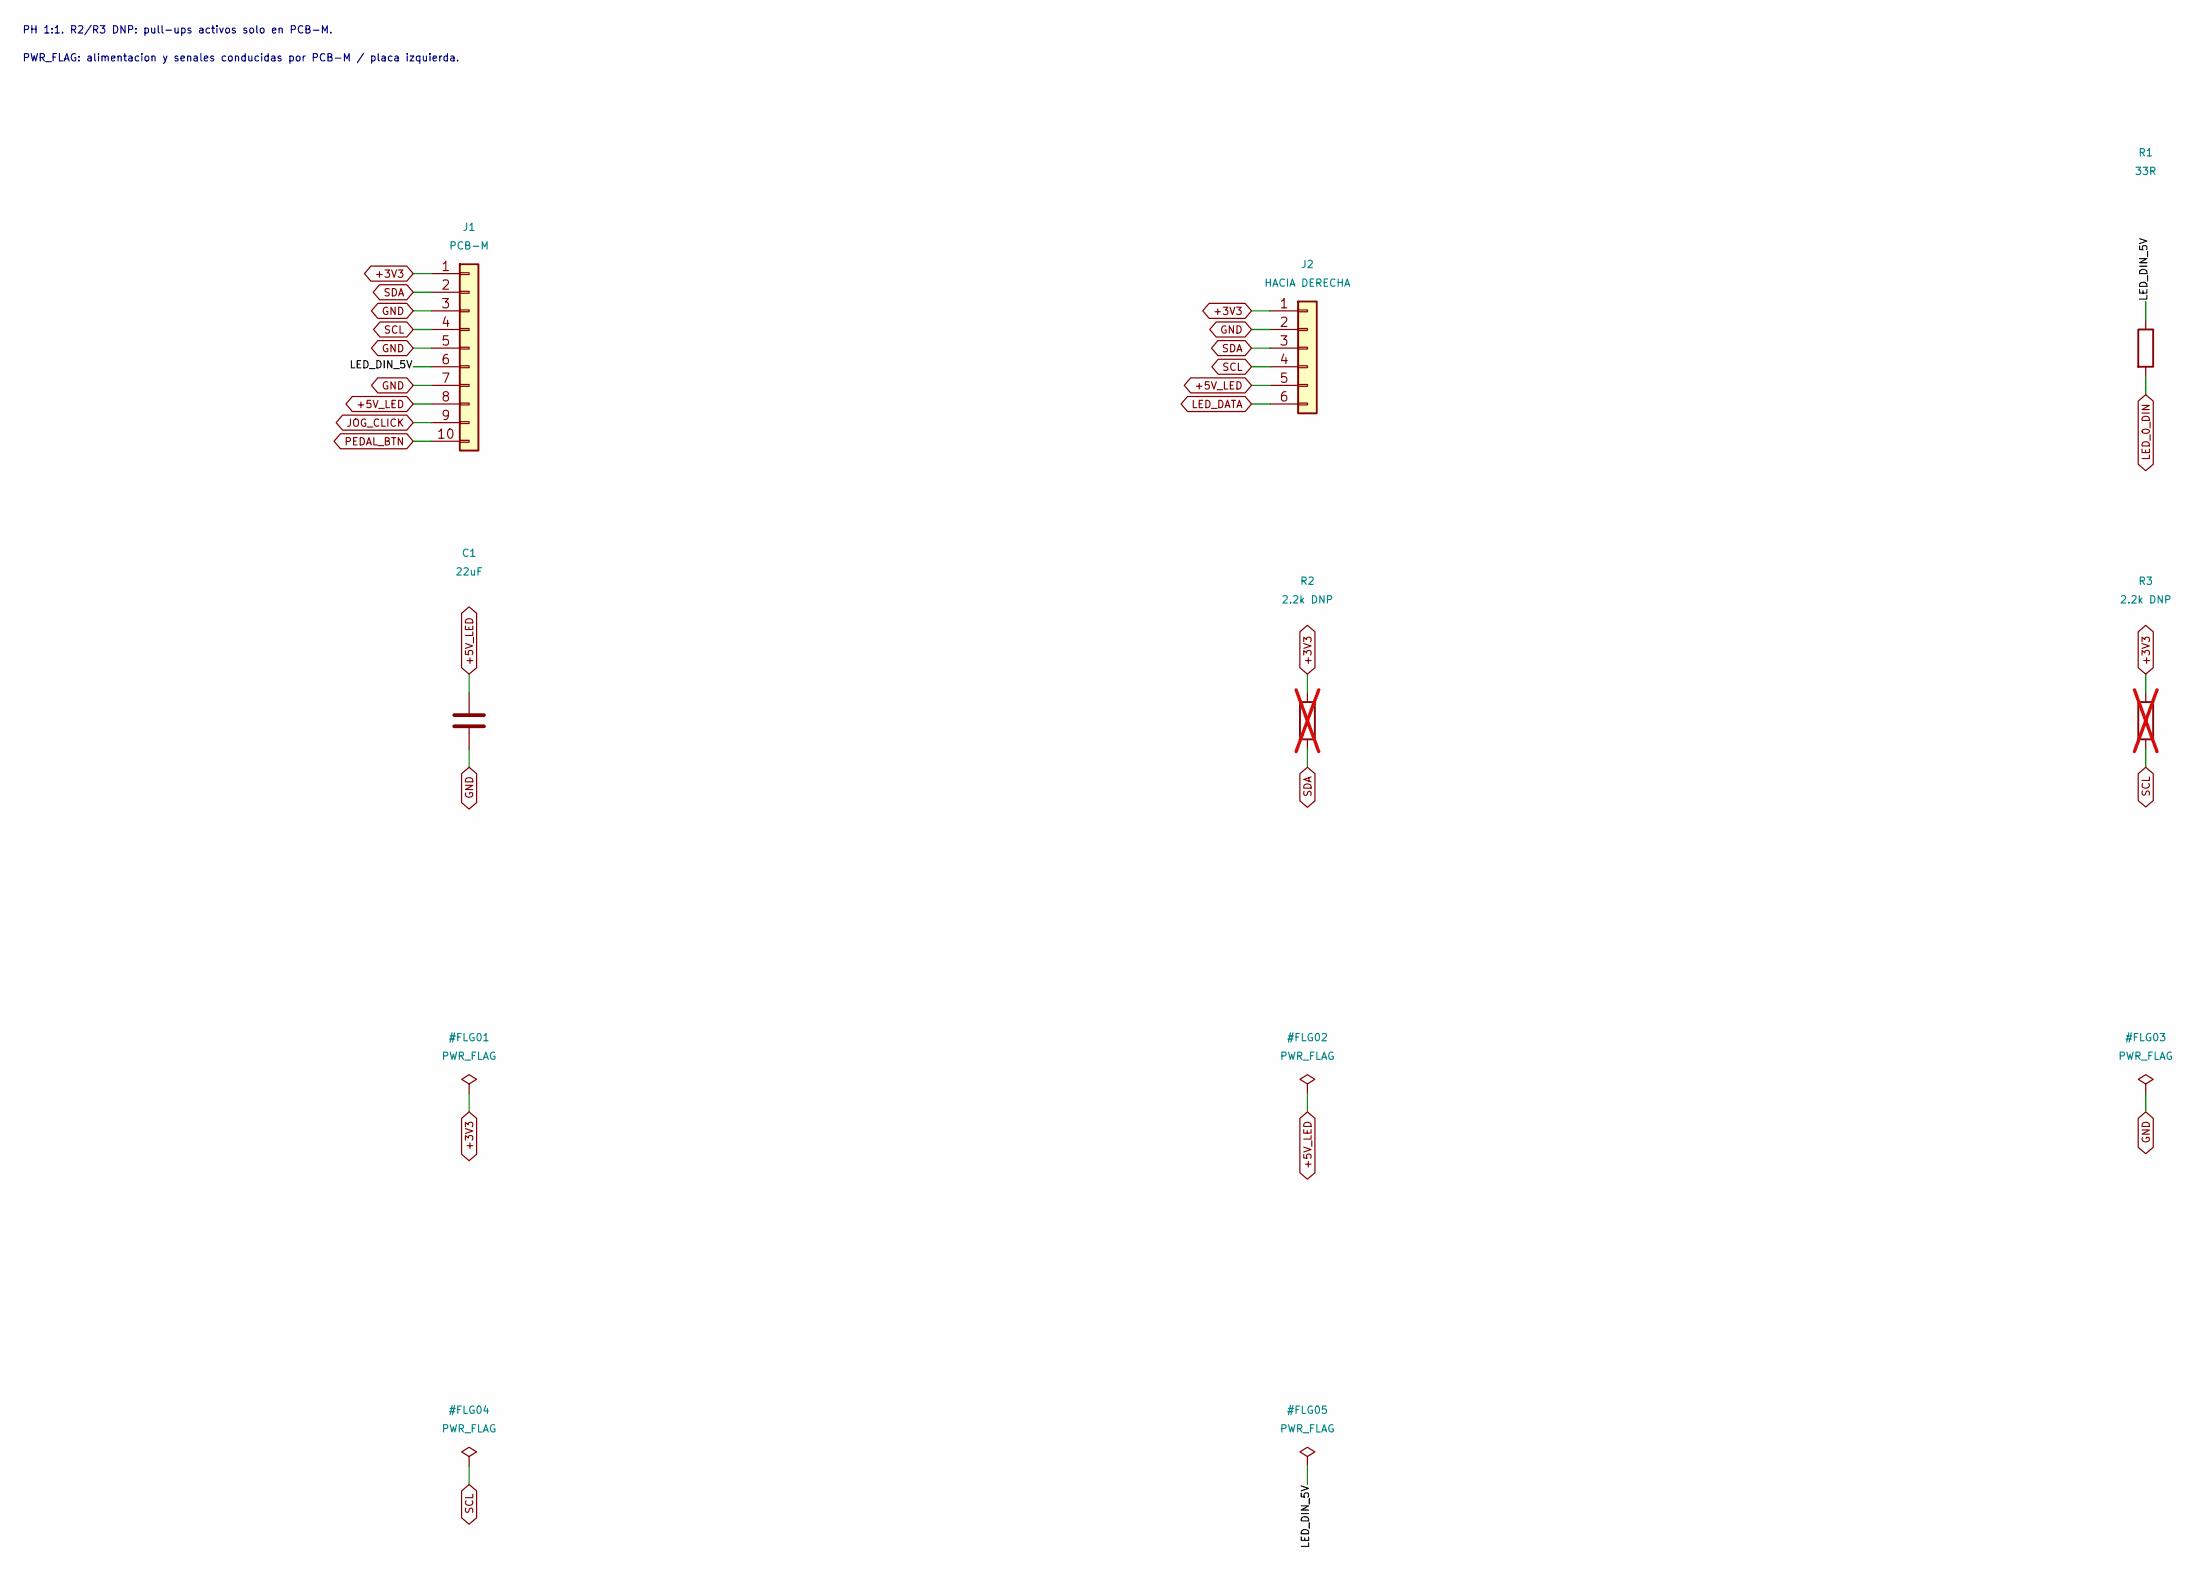
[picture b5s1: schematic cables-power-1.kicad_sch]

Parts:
C1: 22uF; C_1206_3216Metric; MPN CL31A226KAHNNNE; LCSC C12891
J1: PCB-M; JST_PH_B10B-PH-K_1x10_P2.00mm_Vertical; MPN B10B-PH-K-S(LF)(SN); LCSC C158038
J2: HACIA DERECHA; JST_PH_B6B-PH-K_1x06_P2.00mm_Vertical; MPN B6B-PH-K-S(LF)(SN); LCSC C131342
R1: 33R; R_0805_2012Metric; MPN 0805W8F330JT5E; LCSC C17634
R2, R3: 2.2k DNP; R_0805_2012Metric; MPN 0805W8F2201T5E; LCSC C17520; not fitted

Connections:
+3V3: J1.1, J2.1, R2.1, R3.1; also elsewhere on the board
+5V_LED: C1.1, J1.8, J2.5; also elsewhere on the board
/cables-power-1/LED_DIN_5V: J1.6, R1.1
GND: C1.2, J1.3, J1.5, J1.7, J2.2; also elsewhere on the board
JOG_CLICK: J1.9; also elsewhere on the board
LED_0_DIN: R1.2; also elsewhere on the board
LED_DATA: J2.6; also elsewhere on the board
PEDAL_BTN: J1.10; also elsewhere on the board
SCL: J1.4, J2.4, R3.2; also elsewhere on the board
SDA: J1.2, J2.3, R2.2; also elsewhere on the board

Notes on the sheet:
PH 1:1. R2/R3 DNP: pull-ups activos solo en PCB-M.
PWR_FLAG: alimentacion y senales conducidas por PCB-M / placa izquierda.
